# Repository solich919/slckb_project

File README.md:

# slckb_project
Keyboard project based on AVR

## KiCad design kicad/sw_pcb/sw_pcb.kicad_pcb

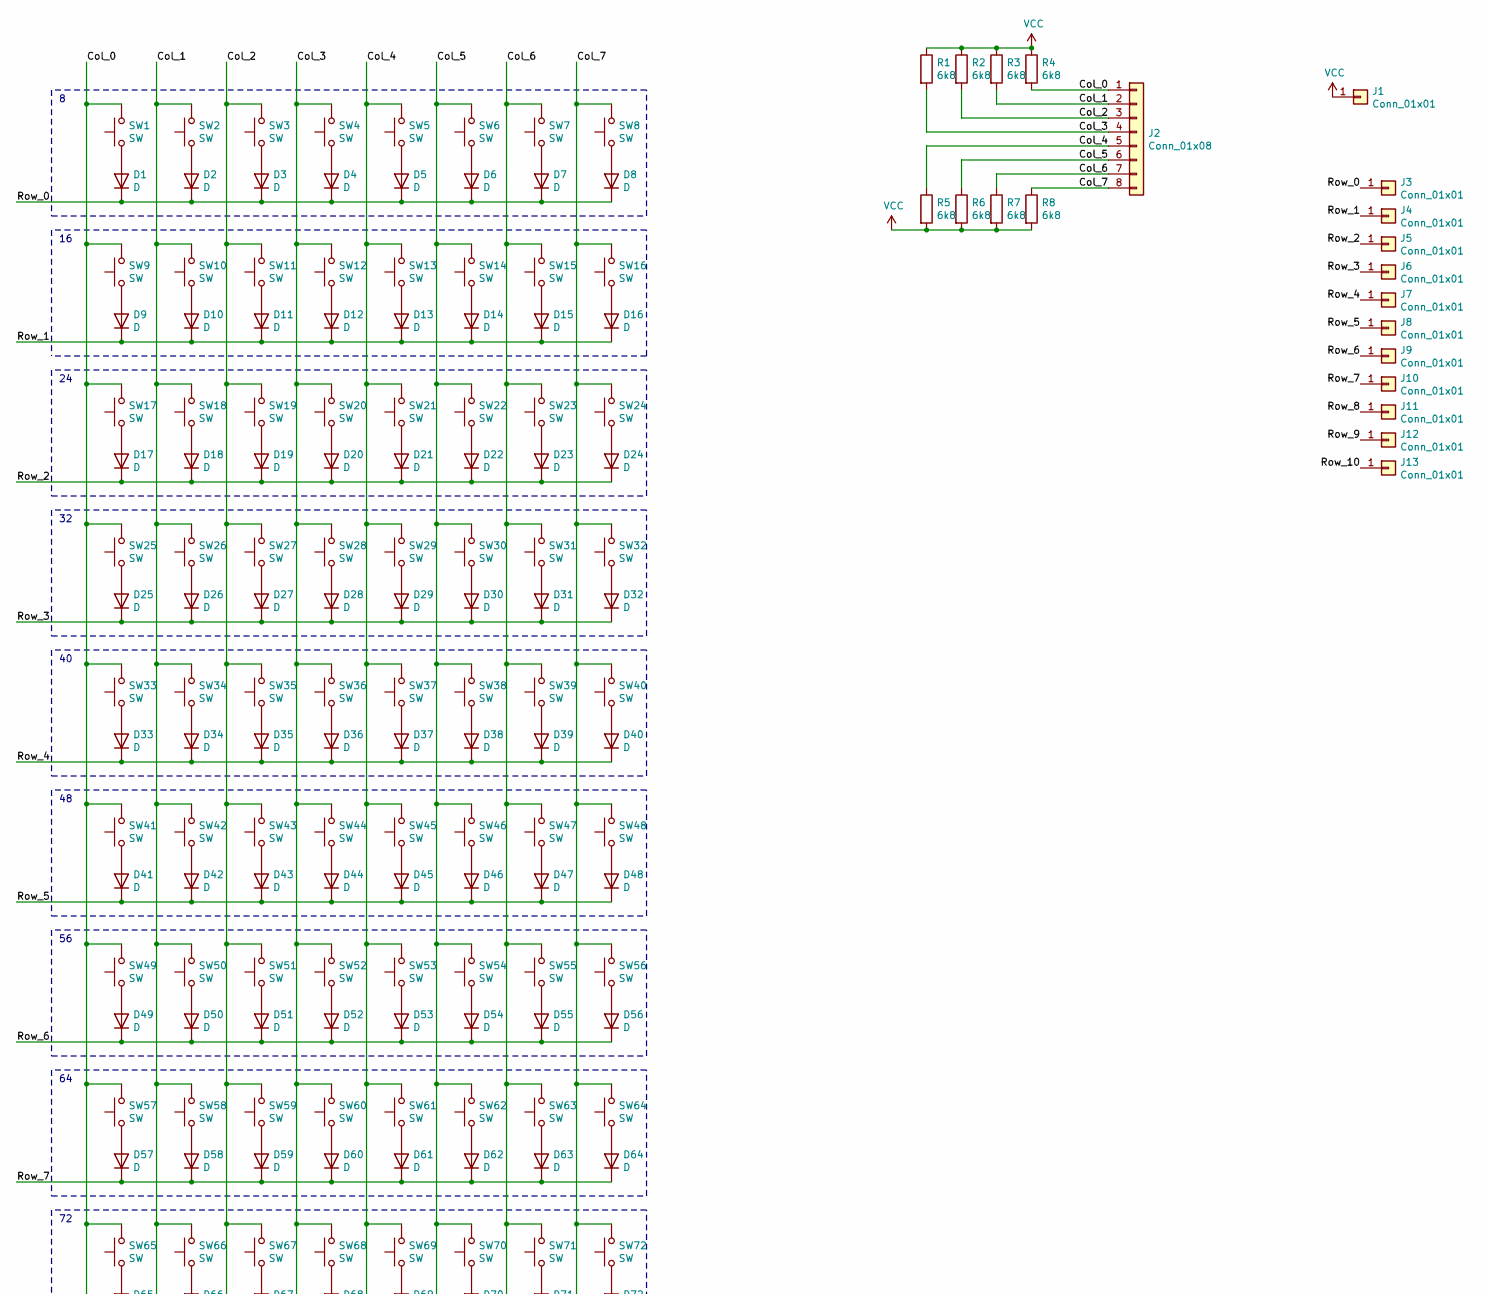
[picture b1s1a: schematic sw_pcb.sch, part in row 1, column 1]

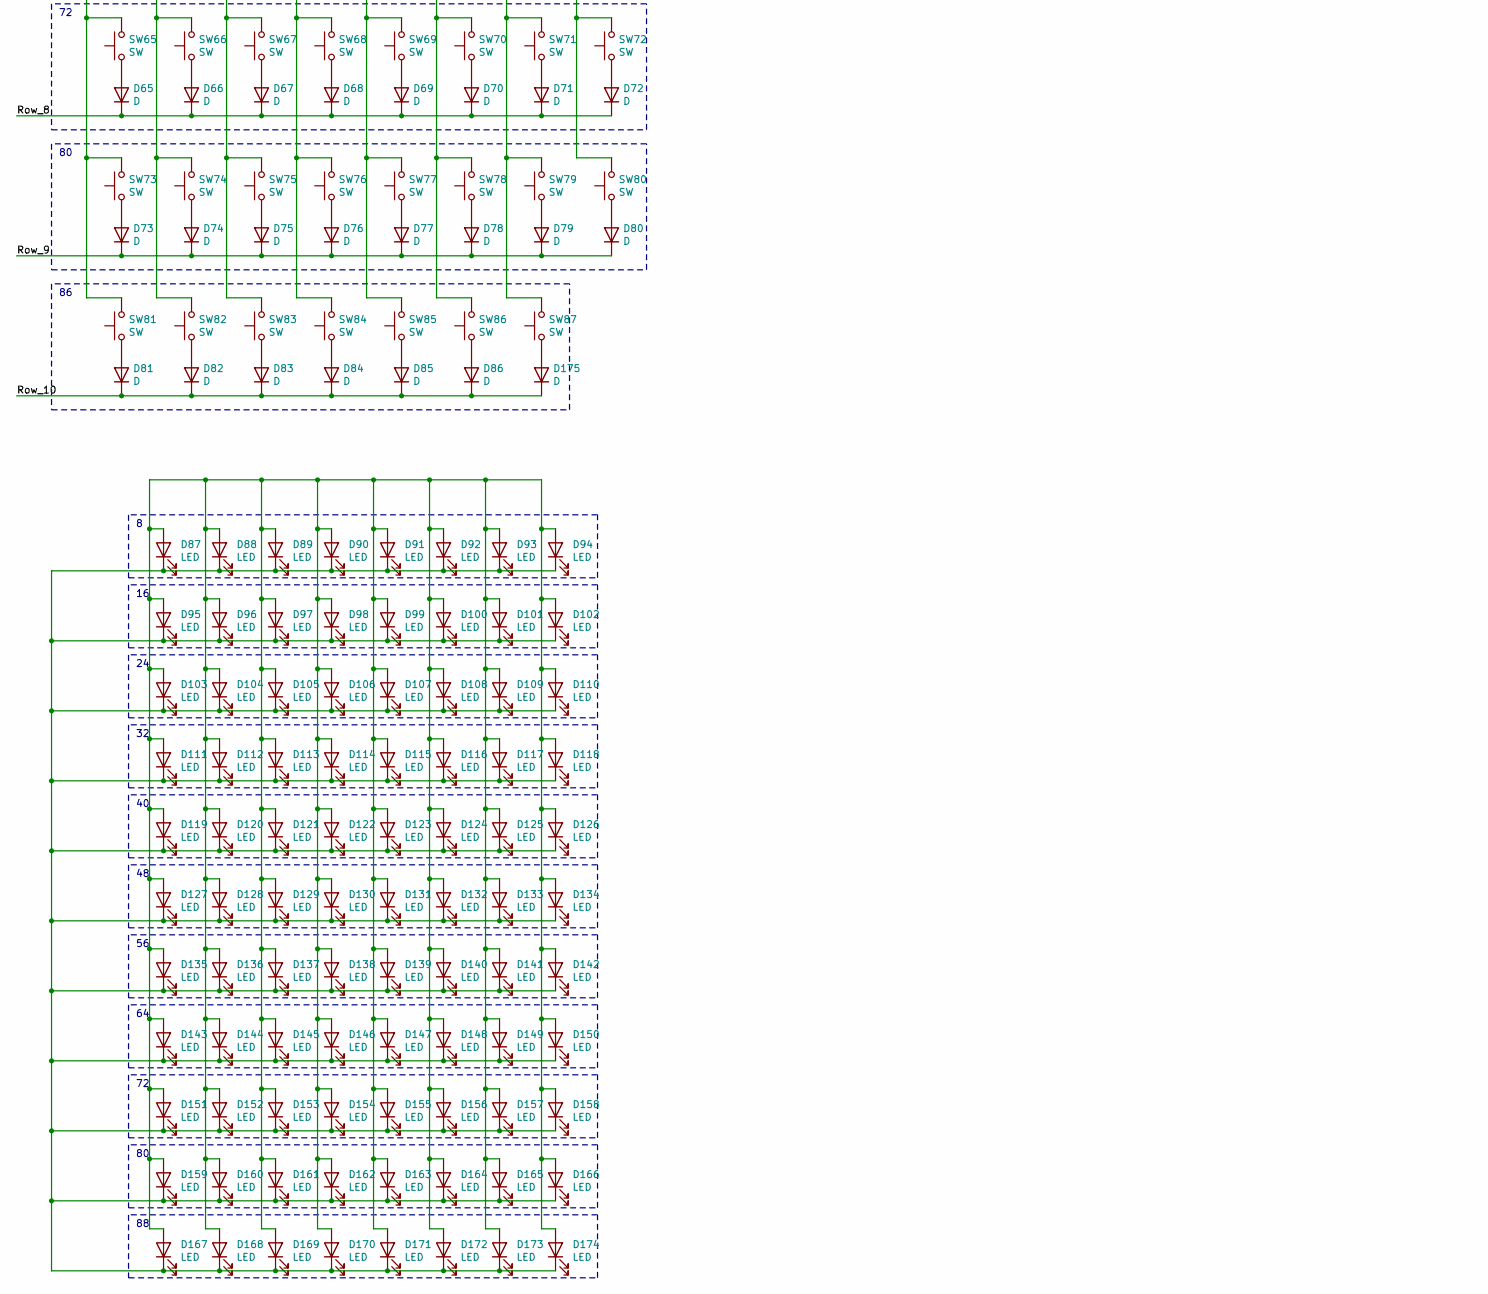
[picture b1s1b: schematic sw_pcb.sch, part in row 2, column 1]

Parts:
D1, D2, D3, D4, D5, D6, D7, D8, D9, D10, D11, D12, D13, D14, D15, D16, D17, D18, D19, D20, D21, D22, D23, D24, D25, D26, D27, D28, D29, D30, D31, D32, D33, D34, D35, D36, D37, D38, D39, D40, D41, D42, D43, D44, D45, D46, D47, D48, D49, D50, D51, D52, D53, D54, D55, D56, D57, D58, D59, D60, D61, D62, D63, D64, D65, D66, D67, D68, D69, D70, D71, D72, D73, D74, D75, D76, D77, D78, D79, D80, D81, D82, D83, D84, D85, D86, D175: D; D_MicroMELF_Handsoldering
D87, D88, D89, D90, D91, D92, D93, D94, D95, D96, D97, D98, D99, D100, D101, D102, D103, D104, D105, D106, D107, D108, D109, D110, D111, D112, D113, D114, D115, D116, D117, D118, D119, D120, D121, D122, D123, D124, D125, D126, D127, D128, D129, D130, D131, D132, D133, D134, D135, D136, D137, D138, D139, D140, D141, D142, D143, D144, D145, D146, D147, D148, D149, D150, D151, D152, D153, D154, D155, D156, D157, D158, D159, D160, D161, D162, D163, D164, D165, D166, D167, D168, D169, D170, D171, D172, D173, D174: LED
J1, J3, J4, J5, J6, J7, J8, J9, J10, J11, J12, J13: Conn_01x01
J2: Conn_01x08; PinSocket_1x08_P2.54mm_Vertical
R1, R2, R3, R4, R5, R6, R7, R8: 6k8
SW1, SW2, SW3, SW4, SW5, SW6, SW7, SW8, SW9, SW10, SW11, SW12, SW13, SW14, SW15, SW16, SW17, SW18, SW19, SW20, SW21, SW22, SW23, SW24, SW25, SW26, SW27, SW28, SW29, SW30, SW33, SW34, SW35, SW36, SW37, SW38, SW39, SW40, SW41, SW42, SW43, SW44, SW45, SW48, SW49, SW50, SW51, SW52, SW53, SW54, SW55, SW56, SW57, SW58, SW59, SW62, SW63, SW64, SW65, SW66, SW67, SW68, SW69, SW70, SW71, SW72, SW82, SW83, SW84, SW85, SW86, SW87: SW; SW_Cherry_MX_PCB_1.00u
SW31: SW; SW_Cherry_MX_PCB_2.00u
SW32, SW46: SW; SW_Cherry_MX_PCB_1.50u
SW47: SW; SW_Cherry_MX_PCB_1.75u
SW60, SW61: SW; SW_Cherry_MX_PCB_2.25u
SW73: SW; SW_Cherry_MX_PCB_2.75u
SW74, SW75, SW76, SW78, SW79, SW80, SW81: SW; SW_Cherry_MX_PCB_1.25u
SW77: SW; SW_Cherry_MX_PCB_6.25u

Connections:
/Col_0: J2.1, R4.2, SW1.2, SW9.2, SW17.2, SW25.2, SW33.2, SW41.2, SW49.2, SW57.2, SW65.2, SW73.2, SW81.2
/Col_1: J2.2, R3.2, SW2.2, SW10.2, SW18.2, SW26.2, SW34.2, SW42.2, SW50.2, SW58.2, SW66.2, SW74.2, SW82.2
/Col_2: J2.3, R2.2, SW3.2, SW11.2, SW19.2, SW27.2, SW35.2, SW43.2, SW51.2, SW59.2, SW67.2, SW75.2, SW83.2
/Col_3: J2.4, R1.2, SW4.2, SW12.2, SW20.2, SW28.2, SW36.2, SW44.2, SW52.2, SW60.2, SW68.2, SW76.2, SW84.2
/Col_4: J2.5, R5.1, SW5.2, SW13.2, SW21.2, SW29.2, SW37.2, SW45.2, SW53.2, SW61.2, SW69.2, SW77.2, SW85.2
/Col_5: J2.6, R6.1, SW6.2, SW14.2, SW22.2, SW30.2, SW38.2, SW46.2, SW54.2, SW62.2, SW70.2, SW78.2, SW86.2
/Col_6: J2.7, R7.1, SW7.2, SW15.2, SW23.2, SW31.2, SW39.2, SW47.2, SW55.2, SW63.2, SW71.2, SW79.2, SW87.2
/Col_7: J2.8, R8.1, SW8.2, SW16.2, SW24.2, SW32.2, SW40.2, SW48.2, SW56.2, SW64.2, SW72.2, SW80.2
/Row_0: D1.1 (K), D2.1 (K), D3.1 (K), D4.1 (K), D5.1 (K), D6.1 (K), D7.1 (K), D8.1 (K), J3.1
/Row_1: D9.1 (K), D10.1 (K), D11.1 (K), D12.1 (K), D13.1 (K), D14.1 (K), D15.1 (K), D16.1 (K), J4.1
/Row_2: D17.1 (K), D18.1 (K), D19.1 (K), D20.1 (K), D21.1 (K), D22.1 (K), D23.1 (K), D24.1 (K), J5.1
/Row_3: D25.1 (K), D26.1 (K), D27.1 (K), D28.1 (K), D29.1 (K), D30.1 (K), D31.1 (K), D32.1 (K), J6.1
/Row_4: D33.1 (K), D34.1 (K), D35.1 (K), D36.1 (K), D37.1 (K), D38.1 (K), D39.1 (K), D40.1 (K), J7.1
/Row_5: D41.1 (K), D42.1 (K), D43.1 (K), D44.1 (K), D45.1 (K), D46.1 (K), D47.1 (K), D48.1 (K), J8.1
/Row_6: D49.1 (K), D50.1 (K), D51.1 (K), D52.1 (K), D53.1 (K), D54.1 (K), D55.1 (K), D56.1 (K), J9.1
/Row_7: D57.1 (K), D58.1 (K), D59.1 (K), D60.1 (K), D61.1 (K), D62.1 (K), D63.1 (K), D64.1 (K), J10.1
/Row_8: D65.1 (K), D66.1 (K), D67.1 (K), D68.1 (K), D69.1 (K), D70.1 (K), D71.1 (K), D72.1 (K), J11.1
/Row_9: D73.1 (K), D74.1 (K), D75.1 (K), D76.1 (K), D77.1 (K), D78.1 (K), D79.1 (K), D80.1 (K), J12.1
/Row_10: D81.1 (K), D82.1 (K), D83.1 (K), D84.1 (K), D85.1 (K), D86.1 (K), D175.1 (K), J13.1
unnamed: D1.2 (A), SW1.1
unnamed: D2.2 (A), SW2.1
unnamed: D3.2 (A), SW3.1
unnamed: D4.2 (A), SW4.1
unnamed: D5.2 (A), SW5.1
unnamed: D6.2 (A), SW6.1
unnamed: D7.2 (A), SW7.1
unnamed: D8.2 (A), SW8.1
unnamed: D9.2 (A), SW9.1
unnamed: D10.2 (A), SW10.1
unnamed: D11.2 (A), SW11.1
unnamed: D12.2 (A), SW12.1
unnamed: D13.2 (A), SW13.1
unnamed: D14.2 (A), SW14.1
unnamed: D15.2 (A), SW15.1
unnamed: D16.2 (A), SW16.1
unnamed: D17.2 (A), SW17.1
unnamed: D18.2 (A), SW18.1
unnamed: D19.2 (A), SW19.1
unnamed: D20.2 (A), SW20.1
unnamed: D21.2 (A), SW21.1
unnamed: D22.2 (A), SW22.1
unnamed: D23.2 (A), SW23.1
unnamed: D24.2 (A), SW24.1
unnamed: D25.2 (A), SW25.1
unnamed: D26.2 (A), SW26.1
unnamed: D27.2 (A), SW27.1
unnamed: D28.2 (A), SW28.1
unnamed: D29.2 (A), SW29.1
unnamed: D30.2 (A), SW30.1
unnamed: D31.2 (A), SW31.1
unnamed: D32.2 (A), SW32.1
unnamed: D33.2 (A), SW33.1
unnamed: D34.2 (A), SW34.1
unnamed: D35.2 (A), SW35.1
unnamed: D36.2 (A), SW36.1
unnamed: D37.2 (A), SW37.1
unnamed: D38.2 (A), SW38.1
unnamed: D39.2 (A), SW39.1
unnamed: D40.2 (A), SW40.1
unnamed: D41.2 (A), SW41.1
unnamed: D42.2 (A), SW42.1
unnamed: D43.2 (A), SW43.1
unnamed: D44.2 (A), SW44.1
unnamed: D45.2 (A), SW45.1
unnamed: D46.2 (A), SW46.1
unnamed: D47.2 (A), SW47.1
unnamed: D48.2 (A), SW48.1
unnamed: D49.2 (A), SW49.1
unnamed: D50.2 (A), SW50.1
unnamed: D51.2 (A), SW51.1
unnamed: D52.2 (A), SW52.1
unnamed: D53.2 (A), SW53.1
unnamed: D54.2 (A), SW54.1
unnamed: D55.2 (A), SW55.1
unnamed: D56.2 (A), SW56.1
unnamed: D57.2 (A), SW57.1
unnamed: D58.2 (A), SW58.1
unnamed: D59.2 (A), SW59.1
unnamed: D60.2 (A), SW60.1
unnamed: D61.2 (A), SW61.1
unnamed: D62.2 (A), SW62.1
unnamed: D63.2 (A), SW63.1
unnamed: D64.2 (A), SW64.1
unnamed: D65.2 (A), SW65.1
unnamed: D66.2 (A), SW66.1
unnamed: D67.2 (A), SW67.1
unnamed: D68.2 (A), SW68.1
unnamed: D69.2 (A), SW69.1
unnamed: D70.2 (A), SW70.1
unnamed: D71.2 (A), SW71.1
unnamed: D72.2 (A), SW72.1
unnamed: D73.2 (A), SW73.1
unnamed: D74.2 (A), SW74.1
unnamed: D75.2 (A), SW75.1
unnamed: D76.2 (A), SW76.1
unnamed: D77.2 (A), SW77.1
unnamed: D78.2 (A), SW78.1
unnamed: D79.2 (A), SW79.1
unnamed: D80.2 (A), SW80.1
unnamed: D81.2 (A), SW81.1
unnamed: D82.2 (A), SW82.1
unnamed: D83.2 (A), SW83.1
unnamed: D84.2 (A), SW84.1
unnamed: D85.2 (A), SW85.1
unnamed: D86.2 (A), SW86.1
unnamed: D87.1 (K), D88.1 (K), D89.1 (K), D90.1 (K), D91.1 (K), D92.1 (K), D93.1 (K), D94.1 (K), D95.1 (K), D96.1 (K), D97.1 (K), D98.1 (K), D99.1 (K), D100.1 (K), D101.1 (K), D102.1 (K), D103.1 (K), D104.1 (K), D105.1 (K), D106.1 (K), D107.1 (K), D108.1 (K), D109.1 (K), D110.1 (K), D111.1 (K), D112.1 (K), D113.1 (K), D114.1 (K), D115.1 (K), D116.1 (K), D117.1 (K), D118.1 (K), D119.1 (K), D120.1 (K), D121.1 (K), D122.1 (K), D123.1 (K), D124.1 (K), D125.1 (K), D126.1 (K), D127.1 (K), D128.1 (K), D129.1 (K), D130.1 (K), D131.1 (K), D132.1 (K), D133.1 (K), D134.1 (K), D135.1 (K), D136.1 (K), D137.1 (K), D138.1 (K), D139.1 (K), D140.1 (K), D141.1 (K), D142.1 (K), D143.1 (K), D144.1 (K), D145.1 (K), D146.1 (K), D147.1 (K), D148.1 (K), D149.1 (K), D150.1 (K), D151.1 (K), D152.1 (K), D153.1 (K), D154.1 (K), D155.1 (K), D156.1 (K), D157.1 (K), D158.1 (K), D159.1 (K), D160.1 (K), D161.1 (K), D162.1 (K), D163.1 (K), D164.1 (K), D165.1 (K), D166.1 (K), D167.1 (K), D168.1 (K), D169.1 (K), D170.1 (K), D171.1 (K), D172.1 (K), D173.1 (K), D174.1 (K)
unnamed: D87.2 (A), D88.2 (A), D89.2 (A), D90.2 (A), D91.2 (A), D92.2 (A), D93.2 (A), D94.2 (A), D95.2 (A), D96.2 (A), D97.2 (A), D98.2 (A), D99.2 (A), D100.2 (A), D101.2 (A), D102.2 (A), D103.2 (A), D104.2 (A), D105.2 (A), D106.2 (A), D107.2 (A), D108.2 (A), D109.2 (A), D110.2 (A), D111.2 (A), D112.2 (A), D113.2 (A), D114.2 (A), D115.2 (A), D116.2 (A), D117.2 (A), D118.2 (A), D119.2 (A), D120.2 (A), D121.2 (A), D122.2 (A), D123.2 (A), D124.2 (A), D125.2 (A), D126.2 (A), D127.2 (A), D128.2 (A), D129.2 (A), D130.2 (A), D131.2 (A), D132.2 (A), D133.2 (A), D134.2 (A), D135.2 (A), D136.2 (A), D137.2 (A), D138.2 (A), D139.2 (A), D140.2 (A), D141.2 (A), D142.2 (A), D143.2 (A), D144.2 (A), D145.2 (A), D146.2 (A), D147.2 (A), D148.2 (A), D149.2 (A), D150.2 (A), D151.2 (A), D152.2 (A), D153.2 (A), D154.2 (A), D155.2 (A), D156.2 (A), D157.2 (A), D158.2 (A), D159.2 (A), D160.2 (A), D161.2 (A), D162.2 (A), D163.2 (A), D164.2 (A), D165.2 (A), D166.2 (A), D167.2 (A), D168.2 (A), D169.2 (A), D170.2 (A), D171.2 (A), D172.2 (A), D173.2 (A), D174.2 (A)
unnamed: D175.2 (A), SW87.1
unnamed: J1.1, R1.1, R2.1, R3.1, R4.1, R5.2, R6.2, R7.2, R8.2

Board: 2 copper layers, 263 parts (0 on the bottom side), 108 nets, no tracks yet.

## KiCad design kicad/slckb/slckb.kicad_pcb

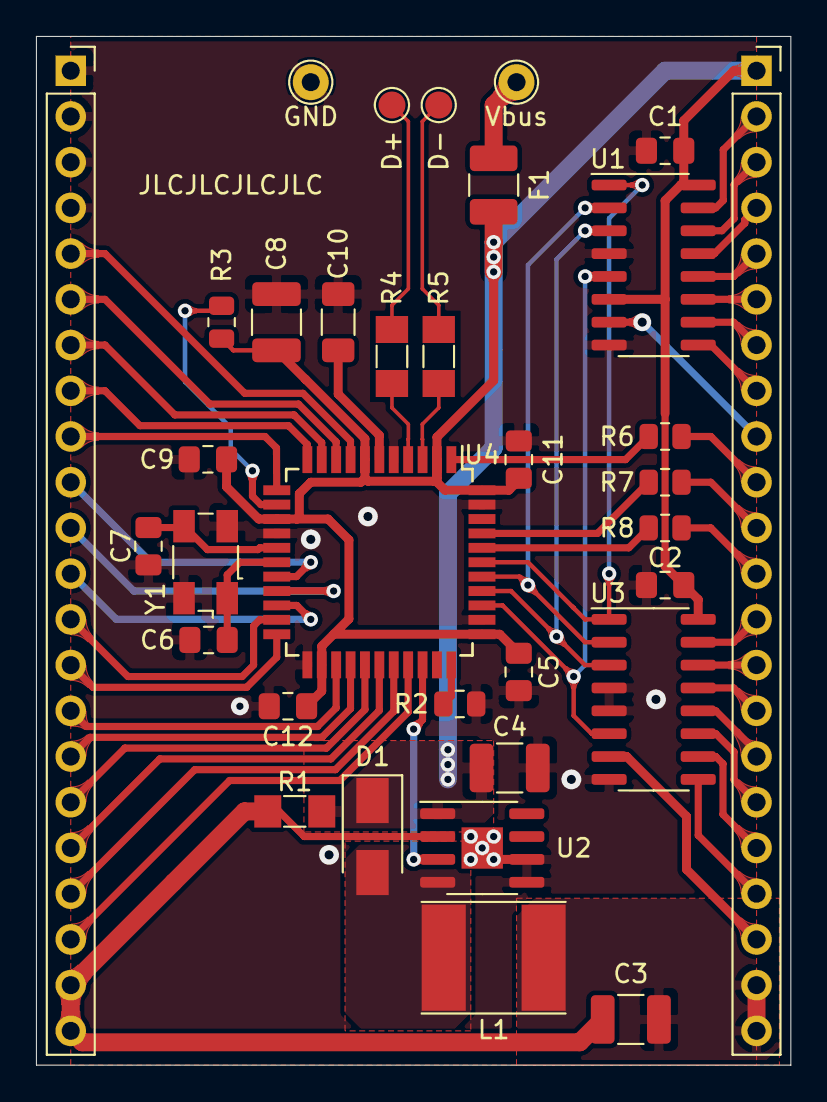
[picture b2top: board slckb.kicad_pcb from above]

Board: 2 copper layers, 41.9 x 57.1 mm, 35 parts (1 on the bottom side), 58 nets.

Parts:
C1, C2, C5, C9, C11, C12: 100n; C_0805_2012Metric_Pad1.18x1.45mm_HandSolder
C3, C4, C8: 10u; C_1210_3225Metric_Pad1.33x2.70mm_HandSolder
C6, C7: 10p; C_0805_2012Metric_Pad1.18x1.45mm_HandSolder
C10: 1u; C_1206_3216Metric_Pad1.33x1.80mm_HandSolder
D1: B1100; D_SMA
D+: Conn_01x01; TestPoint_Pad_D1.5mm
D-: Conn_01x01; TestPoint_Pad_D1.5mm
F1: 500m; Fuse_1210_3225Metric_Pad1.42x2.65mm_HandSolder
GND: Conn_01x01; TestPoint_THTPad_D2.0mm_Drill1.0mm
J1, J3: Conn_01x22_Female; PinSocket_1x22_P2.54mm_Vertical
L1: DJNR6045-680; L_Taiyo-Yuden_NR-60xx_HandSoldering
R1: 270m; R_MiniMELF_MMA-0204
R2, R3, R6, R7, R8: 6k8; R_0805_2012Metric
R4, R5: 22R; R_MiniMELF_MMA-0204
SW2: SW_Push; SW_SPST_FSMSM
U1, U3: 74AHC138; SOIC-16_3.9x9.9mm_P1.27mm
U2: SCT2932; HSOP-8-1EP_3.9x4.9mm_P1.27mm_EP2.3x2.3mm
U4: ATmega32U4-AU; TQFP-44_10x10mm_P0.8mm
Vbus: Conn_01x01; TestPoint_THTPad_D2.0mm_Drill1.0mm
Y1: Crystal_GND24; Crystal_SMD_Abracon_ABM3B-4Pin_5.0x3.2mm

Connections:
/1: J1.5, U4.8
/2: J1.6, U4.9
/3: J1.7, U4.10
/4: J1.8, U4.11
/5: J1.9, U4.12
/6: J1.10, U4.18
/7: J1.11, U4.19
/8: J1.12, U4.20
/9: J1.13, U4.21
/10: J1.14, U4.22
/11: J1.15, U4.25
/12: J1.16, U4.26
/13: J1.17, U4.27
/14: J1.18, U4.28
/15: J1.19, U4.29
/16: J1.20, U4.30
/A0: U1.1, U3.1, U4.39
/A1: U1.2, U3.2, U4.38
/A2: U1.3, U3.3, U4.37
/A3: U1.5, U3.6, U4.36
/CAPS_LOCK: J3.10, R6.2
/D+: D+.1, R4.2
/D-: D-.1, R5.2
/HWB: R2.2, U4.33
/LED_A: C3.1, J1.21, J1.22, R1.1, U2.2
/LED_K: C3.2, J3.21, J3.22, L1.1
/NUM_LOCK: J3.11, R7.2
/PWM: U2.3, U4.31
/RST: R3.1, SW2.1, U4.13
/SCROLL_LOCK: J3.12, R8.2
/XTAL1: C6.1, U4.17, Y1.1
/XTAL2: C7.2, U4.16, Y1.3
/_D+: R4.1, U4.4
/_D-: R5.1, U4.3
GNDD: C1.2, C2.2, C4.2, C5.2, C6.2, C7.1, C8.2, C9.2, C10.2, C11.2, C12.2, GND.1, J1.1, J1.2, J1.3, J1.4, R2.1, SW2.2, U1.4, U1.8, U2.5, U2.6, U2.9, U3.4, U3.5, U3.8, U4.5, U4.15, U4.23, U4.35, U4.43, Y1.2, Y1.4
unnamed: C10.1, U4.6
unnamed: D1.2, L1.2, U2.4
unnamed: F1.2, Vbus.1
unnamed: J3.2, U1.15
unnamed: J3.3, U1.14
unnamed: J3.4, U1.13
unnamed: J3.5, U1.12
unnamed: J3.6, U1.11
unnamed: J3.7, U1.10
unnamed: J3.8, U1.9
unnamed: J3.9, U1.7
unnamed: J3.13, U3.15
unnamed: J3.14, U3.14
unnamed: J3.15, U3.13
unnamed: J3.16, U3.12
unnamed: J3.17, U3.11
unnamed: J3.18, U3.10
unnamed: J3.19, U3.9
unnamed: J3.20, U3.7
unnamed: R6.1, U4.1
unnamed: R7.1, U4.41
unnamed: R8.1, U4.40
VBUS: C1.1, C2.1, C4.1, C5.1, C8.1, C9.1, C11.1, C12.1, D1.1, F1.1, J3.1, R1.2, R3.2, U1.6, U1.16, U2.1, U3.16, U4.2, U4.7, U4.14, U4.24, U4.34, U4.44

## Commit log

2020-10-28 Rename doc.tex to doc/doc.tex
2020-10-28 Create t
2020-11-02 Pierwszy commit
2020-11-03 fundament
2020-11-03 added TKL pcb schematics
2020-11-04 removed bak files, updated TODO
2020-11-04 general update
2020-11-17 some updates
2020-11-18 doc update
2020-11-28 updated makefile
2020-11-28 updated gitignore
2020-11-28 added comments for makefile
2020-11-29 updated TODO
2020-11-29 updated lib, added string
2020-11-29 Some preparations for further work
2020-11-29 seperated uart functions
2020-11-29 small changes
2020-11-29 small syntax tweak
